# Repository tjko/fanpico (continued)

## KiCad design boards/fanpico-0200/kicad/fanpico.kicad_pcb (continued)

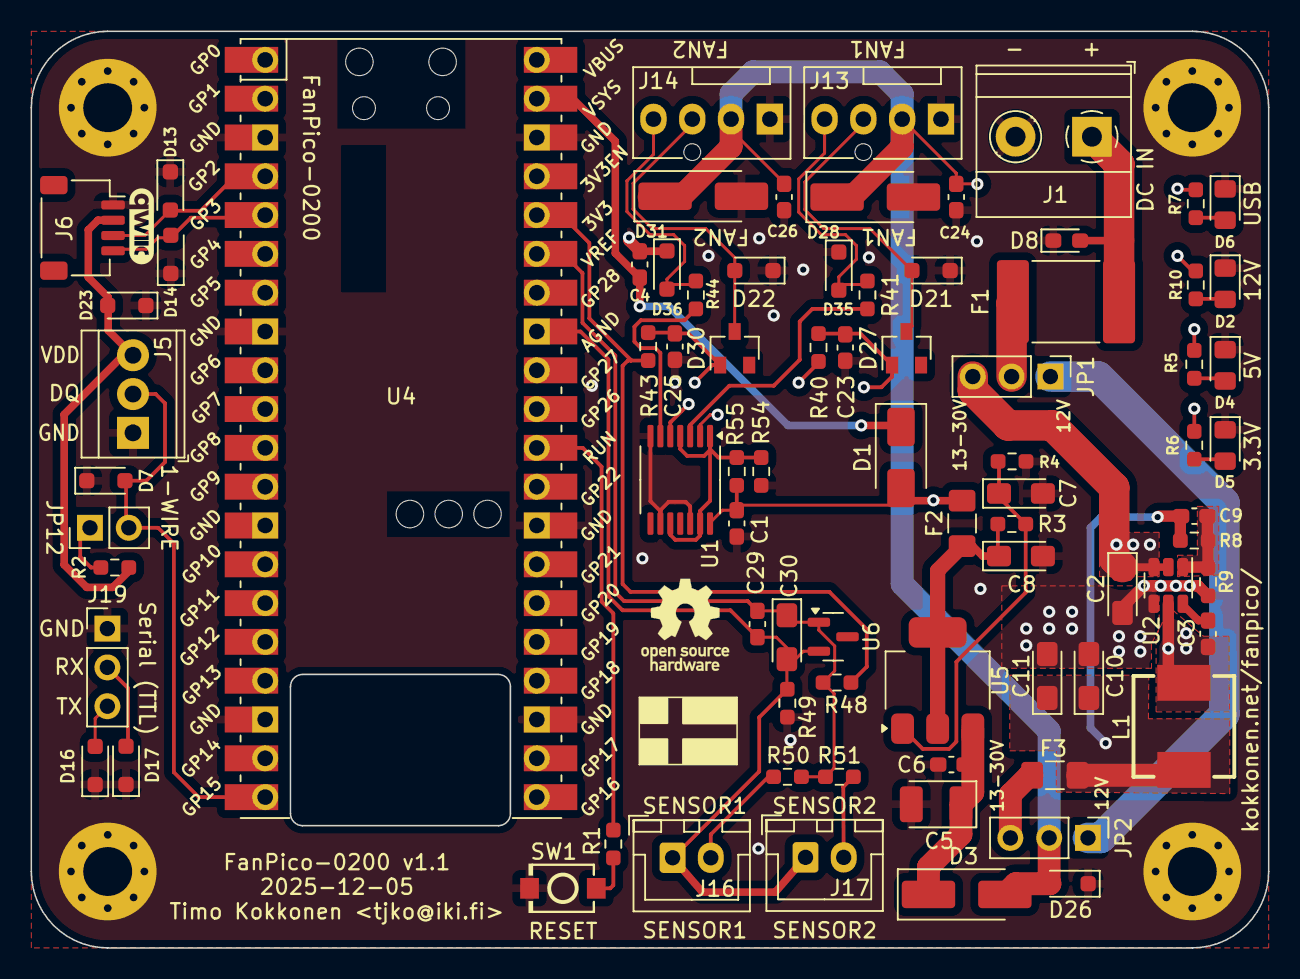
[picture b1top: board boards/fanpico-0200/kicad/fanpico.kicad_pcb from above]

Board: 4 copper layers, 81.0 x 60.0 mm, 86 parts (0 on the bottom side), 45 nets.

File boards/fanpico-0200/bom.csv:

"Reference","Value","Datasheet","Footprint","Qty","DNP","Mouser Part Number","LCSC Part Number","Manufacturer","Manufacturer Part Number","Type","Notes"
"C1,C3,C4,C6,C24,C26,C29","0.1uF 50V","~","Capacitor_SMD:C_0603_1608Metric_Pad1.08x0.95mm_HandSolder","7","","","C1591","Samsung Electro-Mechanics","CL10B104KB8NNNC","SMD",""
"C2","10uF 50V","~","Capacitor_Tantalum_SMD:CP_EIA-3216-18_Kemet-A_Pad1.58x1.35mm_HandSolder","1","","","C89632","Samsung Electro-Mechanics","CL31B106KBHNNNE","SMD",""
"C5","10uF 25V","~","Capacitor_Tantalum_SMD:CP_EIA-3528-12_Kemet-T_Pad1.50x2.35mm_HandSolder","1","","","C7194","Kyocera AVX","TAJB106K025RNJ","SMD",""
"C7,C8,C30","10uF 16V","~","Capacitor_Tantalum_SMD:CP_EIA-3216-18_Kemet-A_Pad1.58x1.35mm_HandSolder","3","","80--T491A106K016","C7171","Kyocera AVX","TAJA106K016RNJ","SMD",""
"C9","12pF 50V","~","Capacitor_SMD:C_0603_1608Metric_Pad1.08x0.95mm_HandSolder","1","","","C38523","Samsung Electro-Mechanics","CL10C120JB8NNNC","SMD",""
"C10,C11","22uF 25V","~","Capacitor_Tantalum_SMD:CP_EIA-3216-18_Kemet-A_Pad1.58x1.35mm_HandSolder","2","","","C12891","Samsung Electro-Mechanics","CL31A226KAHNNNE","SMD",""
"C23,C25","1nF 50V","~","Capacitor_SMD:C_0603_1608Metric_Pad1.08x0.95mm_HandSolder","2","","","C1588","Samsung Electro-Mechanics","CL10B102KB8NNNC","SMD",""
"D1","SM5819PL 1A 40V","~","Diode_SMD:D_SMA","1","","833-SM5819PL-TP","C669023","MCC","SM5819PL-TP","SMD",""
"D2,D4,D5,D6","LED 0805 (green)","~","LED_SMD:LED_0805_2012Metric_Pad1.15x1.40mm_HandSolder","4","","710-150080GS75000","C434432","Yongyu Photoelectric","SZYY0805G","SMD",""
"D3,D28,D31","ES1D 1A 200V","~","Diode_SMD:D_SMA_Handsoldering","3","","512-ES1D","C445494","MDD(Microdiode Semiconductor)","ES1D","SMD",""
"D7,D13,D14,D16,D17,D23","3.3V TVS","~","Diode_SMD:D_SOD-323_HandSoldering","6","","","C78439","Brightking","UDD32C03L01","SMD",""
"D8","30V TVS","~","Diode_SMD:D_0603_1608Metric_Pad1.05x0.95mm_HandSolder","1","","","C7473181","MSKSEMI","PESD0603MS30-MS","SMD",""
"D21,D22,D26","12V TVS","~","Diode_SMD:D_SOD-323_HandSoldering","3","","","C5199168","ElecSuper","UDD32C12L01-ES","SMD","C502541"
"D27,D30","BAT54(C)","~","FanPico:D_SOT-23_ANK","2","","241-BAT54C_R1_00001","C2844172","FUXINSEMI","BAT54C","SMD",""
"D35,D36","5V TVS","~","Diode_SMD:D_SOD-323_HandSoldering","2","","","C5180216","ElecSuper","PESD5V0S1BA-ES","SMD",""
"F1","Polyfuse 2A (48V)","~","Fuse:Fuse_2920_7451Metric_Pad2.10x5.45mm_HandSolder","1","","","C22399926","BHFUSE","BSMD2920-200-48V","SMD",""
"F2","Polyfuse 0.5A","~","Fuse:Fuse_1206_3216Metric_Pad1.42x1.75mm_HandSolder","1","","530-0ZCJ0050AF2E","C70072","TECHFUSE","nSMD035-16V","SMD",""
"F3","Polyfuse 1A","~","Fuse:Fuse_1206_3216Metric_Pad1.42x1.75mm_HandSolder","1","","","C7542958","LUTE","1206L100/30NR","SMD",""
"G1","qwiic_Logo","","sparkfun-qwiic:qwiic_5mm","1","","","","","","",""
"G2","Logo_Open_Hardware_Small","~","Symbol:OSHW-Logo_5.7x6mm_SilkScreen","1","","","","","","",""
"H1,H2,H3,H4","MountingHole_Pad","~","MountingHole:MountingHole_3.2mm_M3_Pad_Via","4","DNP","","","","","",""
"J1","DC Power Input","~","TerminalBlock_Phoenix:TerminalBlock_Phoenix_MKDS-1,5-2_1x02_P5.00mm_Horizontal","1","","651-1715022 ","C1509679","JILN","JL301-50002U04","THT",""
"J5","1-Wire","~","TerminalBlock_TE-Connectivity:TerminalBlock_TE_282834-3_1x03_P2.54mm_Horizontal","1","","","C68305","BOOMELE(Boom Precision Elec)","2.54-3P","THT","C5188443"
"J6","QWIIC","~","Connector_JST:JST_SH_SM04B-SRSS-TB_1x04-1MP_P1.00mm_Horizontal","1","","","C160404","JST","SM04B-SRSS-TB(LF)(SN)","SMD",""
"J13","Fan1 Output","~","Connector:FanPinHeader_1x04_P2.54mm_Vertical","1","","538-47053-1000","C240840","MOLEX","470531000","THT","KF2510-AW 3+1P"
"J14","Fan2 Output","~","Connector:FanPinHeader_1x04_P2.54mm_Vertical","1","","538-47053-1000","C240840","MOLEX","470531000","THT","KF2510-AW 3+1P"
"J16","Sensor1","~","Connector_JST:JST_XH_B2B-XH-A_1x02_P2.50mm_Vertical","1","","","C20079","BOOMELE(Boom Precision Elec)","XH-2A","THT","C33132 (Right-Angle)"
"J17","Sensor2","~","Connector_JST:JST_XH_B2B-XH-A_1x02_P2.50mm_Vertical","1","","","C20079","BOOMELE(Boom Precision Elec)","XH-2A","THT","C33132 (Right-Angle)"
"J19","Serial Console (TTL)","~","Connector_PinHeader_2.54mm:PinHeader_1x03_P2.54mm_Vertical","1","","","C2937625","XFCN","PZ254V-11-03P","THT",""
"JP12","1-Wire PullUp Enable","~","Connector_PinHeader_2.54mm:PinHeader_1x02_P2.54mm_Vertical","1","","","C492401","XFCN","PZ254V-11-02P","THT",""
"L1","10uH","~","FanPico:IND-SMD_L7.2-W6.6_GPSR07X0","1","","","C5189958","SHOU HAN","CYA0630-10UH","SMD",""
"R1,R4","1k","~","Resistor_SMD:R_0603_1608Metric_Pad0.98x0.95mm_HandSolder","2","","","C22548","YAGEO","RC0603FR-071KL","SMD",""
"R2","4.7k","~","Resistor_SMD:R_0603_1608Metric_Pad0.98x0.95mm_HandSolder","1","","","C99782","YAGEO","RC0603FR-074K7L","SMD",""
"R3,R48","330","~","Resistor_SMD:R_0603_1608Metric_Pad0.98x0.95mm_HandSolder","2","","","C105881","YAGEO","RC0603FR-07330RL","SMD",""
"R5,R7,R40,R43,R50,R51","10k","~","Resistor_SMD:R_0603_1608Metric_Pad0.98x0.95mm_HandSolder","6","","","C98220","YAGEO","RC0603FR-0710KL","SMD",""
"R6","4.99k","~","Resistor_SMD:R_0603_1608Metric_Pad0.98x0.95mm_HandSolder","1","","","C114621","YAGEO","RC0603FR-074K99L","SMD",""
"R8","422k","~","Resistor_SMD:R_0603_1608Metric_Pad0.98x0.95mm_HandSolder","1","","","C245966","YAGEO","RC0603FR-07422KL","SMD",""
"R9","30.1k","~","Resistor_SMD:R_0603_1608Metric_Pad0.98x0.95mm_HandSolder","1","","","C23000","UNI-ROYAL","0603WAF3012T5E","SMD",""
"R10","49.9k","~","Resistor_SMD:R_0603_1608Metric_Pad0.98x0.95mm_HandSolder","1","","","C114624","YAGEO","RC0603FR-0749K9L","SMD",""
"R41,R44","680","~","Resistor_SMD:R_0603_1608Metric_Pad0.98x0.95mm_HandSolder","2","","","C115415","YAGEO","RC0603JR-07680RL","SMD",""
"R49,R55","0","~","Resistor_SMD:R_0603_1608Metric_Pad0.98x0.95mm_HandSolder","2","","","C21189","UNI-ROYAL","0603WAF0000T5E","SMD",""
"R54","DNF","~","Resistor_SMD:R_0603_1608Metric_Pad0.98x0.95mm_HandSolder","1","DNP","","C21189","UNI-ROYAL","0603WAF0000T5E","SMD",""
"SW1","SW_Push","~","FanPico:SW-SMD_L3.9-W3.0-P4.45","1","","","C720477","XUNPU","TS-1088-AR02016","SMD",""
"U1","SN74AHCT126","(AHCT125 =  C36365, AHCT126 =  C155177)","Package_SO:TSSOP-14_4.4x5mm_P0.65mm","1","","","C155177","TI","SN74AHCT126PWR","SMD",""
"U2","AP63301","","FanPico:TSOT-26","1","","","C2158003","DIODES","AP63301WU-7","SMD",""
"U4","Pico W","","FanPico:RPi_Pico_PicoW_SMD_TH","1","","","","RaspberryPi","Pico W / Pico 2 W","SMD",""
"U5","SPX1117-ADJ","http://www.diodes.com/datasheets/AP1117.pdf","Package_TO_SOT_SMD:SOT-223-3_TabPin2","1","","","C67402","MaxLinear","SPX1117M3-L/TR","SMD",""
"U6","LM4040DBZ-3","http://www.ti.com/lit/ds/symlink/lm4040-n.pdf","Package_TO_SOT_SMD:SOT-23","1","","","C143326","MAXIM","LM4040AIM3-3.0+T","SMD",""

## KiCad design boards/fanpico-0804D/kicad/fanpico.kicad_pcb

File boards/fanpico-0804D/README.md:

# FANPICO-0804D PCB

PCB Size: 135mm x 81.5mm

## Change Log

v1.3
- Add QWIIC connector (to simplify connecting I2C sensors).
- Add 1-Wire connector
- Change J1 to a combination footprint (allows mounting either Floppy or DC connector).
- Slightly improved ESD protection (TVS diodes added for most connectors)

v1.2c
- Add support for using either SN74AHCT125 or SN74AHCT126 (as U1 and U2).

v1.2b
- C5 was not derated correctly. Replace with 25V part for proper derating.

v1.2
- Add alternate OLED display header with alternate pinout (J2)
- Change J18 header to 2x5 pins (with extra pins often needed for SPI displays)
- Change pull-ups to pull-downs on PWM signal pins on MBFAN inputs.

v1.1
- Add support for direct mounting either Pico or Pico W
- Remove unused footprints
- Fix errata from v1.0
- Errata:
  - JP11 Silkscreen incorrect: 10K and 100K labels should be the otherway around.

v1.0 
- First Prototye
- Based on 0804 v1.3, with added OLED (I2c) display module support
- Errata:
  - U7 pin 7 (VEE) should be grounded.
    Workaround: add solder bridge between pins 7 & 8.

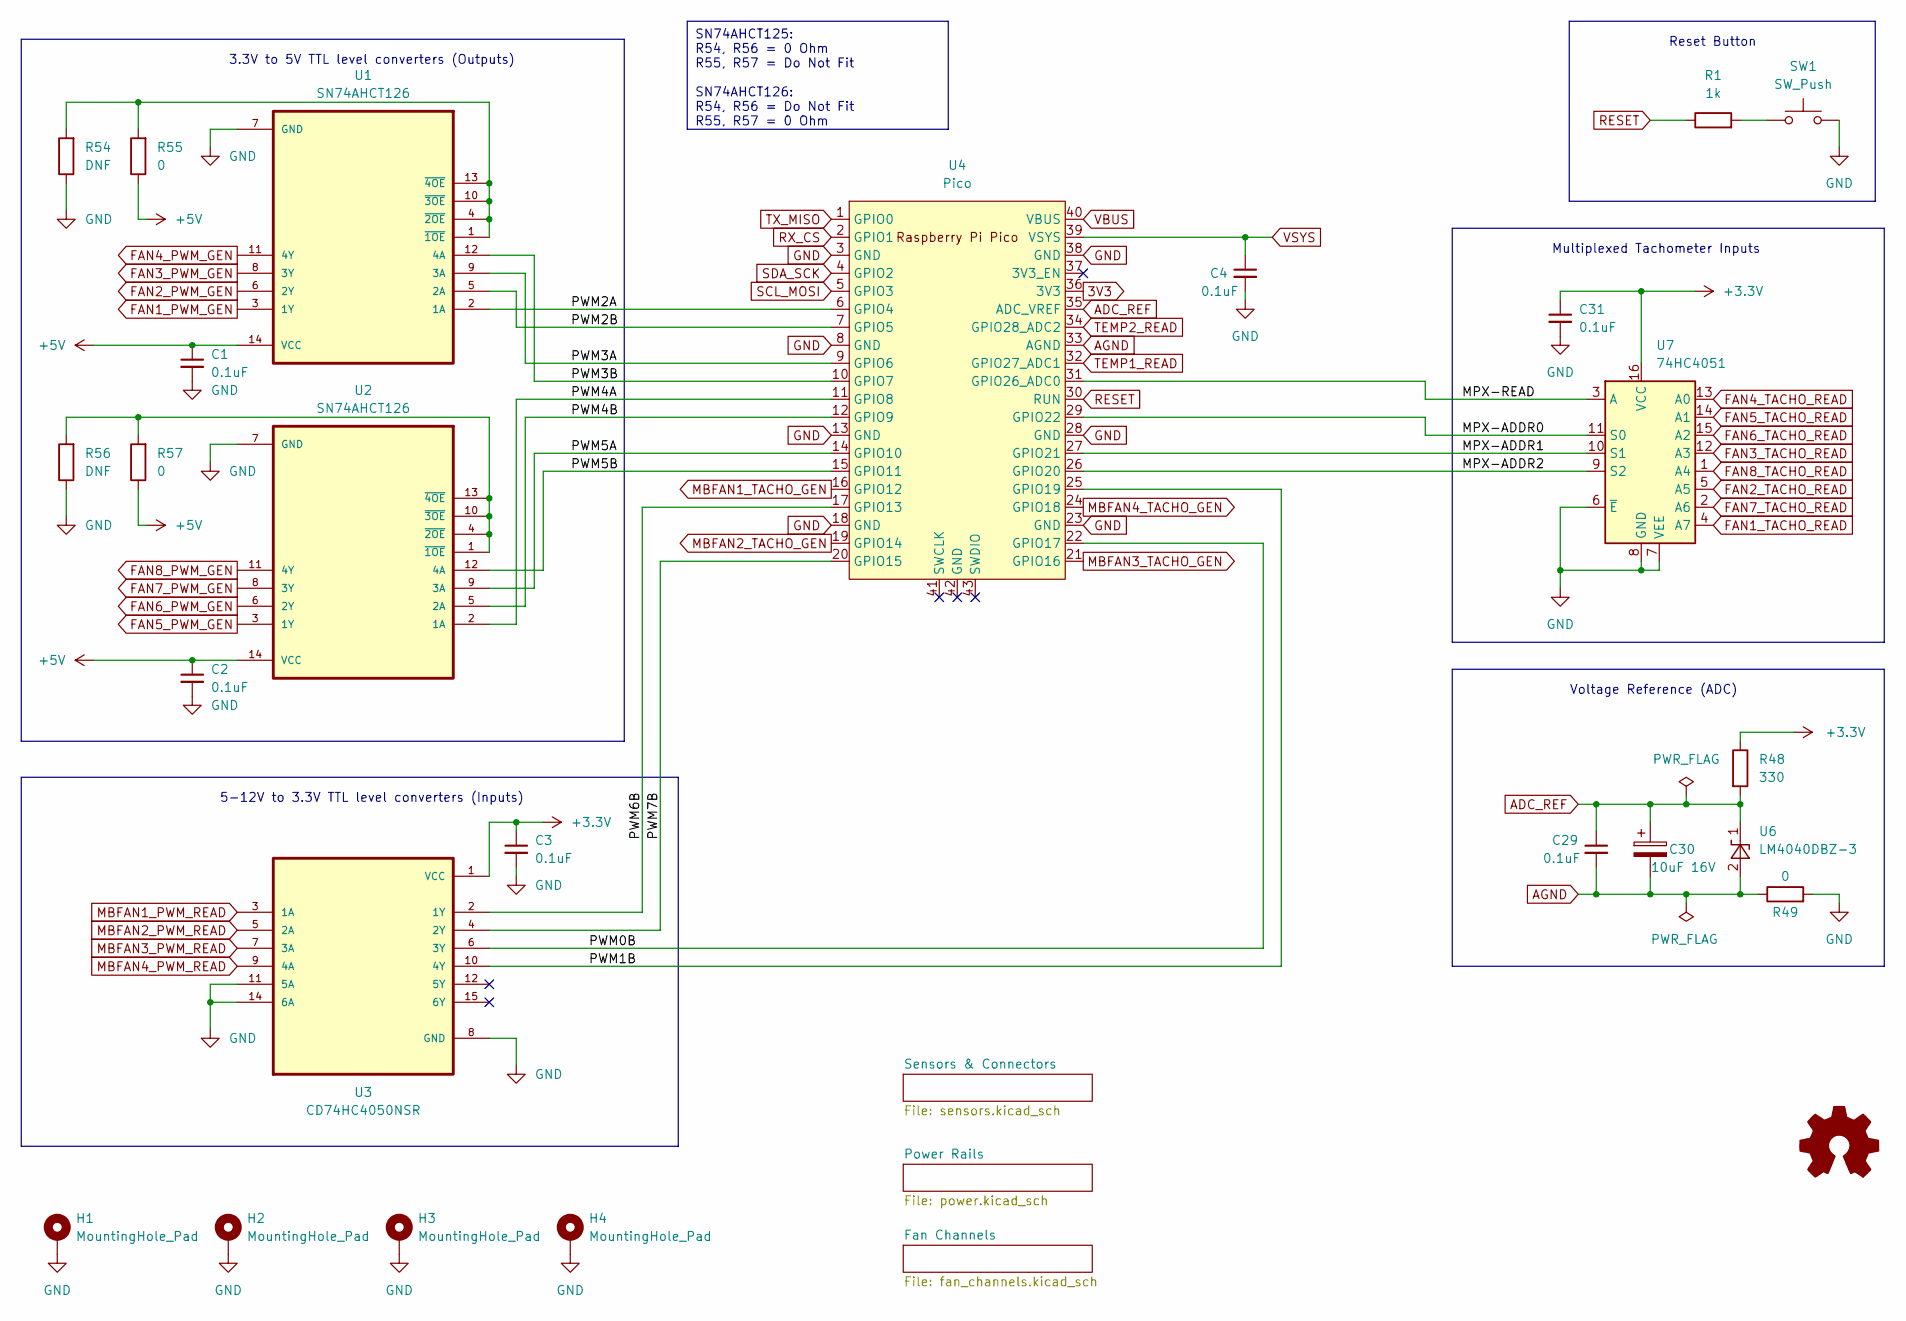
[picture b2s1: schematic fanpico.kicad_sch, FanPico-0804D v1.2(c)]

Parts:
C1, C2, C3, C4, C29, C31: 0.1uF; C_0603_1608Metric_Pad1.08x0.95mm_HandSolder; LCSC Part Number C1591
C30: 10uF 16V; CP_EIA-3216-18_Kemet-A_Pad1.58x1.35mm_HandSolder; LCSC Part Number C7171
H1, H2, H3, H4: MountingHole_Pad; MountingHole_3.2mm_M3_Pad_Via
R1: 1k; R_0603_1608Metric_Pad0.98x0.95mm_HandSolder; LCSC Part Number C22548
R48: 330; R_0603_1608Metric_Pad0.98x0.95mm_HandSolder; LCSC Part Number C105881
R49, R55, R57: 0; R_0603_1608Metric_Pad0.98x0.95mm_HandSolder; LCSC Part Number C21189
R54, R56: DNF; R_0603_1608Metric_Pad0.98x0.95mm_HandSolder
SW1: SW_Push; SW_PUSH_6mm_SMD_2
U1, U2: SN74AHCT126; SOIC-14_3.9x8.7mm_P1.27mm; LCSC Part Number C163728
U3: CD74HC4050NSR; SOIC-16_3.9x9.9mm_P1.27mm; LCSC Part Number C131932
U4: Pico; RPi_Pico_PicoW_SMD_TH
U6: LM4040DBZ-3; SOT-23; LCSC Part Number C143326
U7: 74HC4051; SOIC-16_3.9x9.9mm_P1.27mm; LCSC Part Number C9386

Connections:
3V3: C3.1, C31.1, R48.1, U3.1 (VCC), U4.36 (3V3), U7.16 (VCC); also elsewhere on the board
+5V: C1.1, C2.1, R55.1, R57.1, U1.14 (VCC), U2.14 (VCC); also elsewhere on the board
/MPX-ADDR0: U4.29 (GPIO22), U7.11 (S0)
/MPX-ADDR1: U4.27 (GPIO21), U7.10 (S1)
/MPX-ADDR2: U4.26 (GPIO20), U7.9 (S2)
/MPX-READ: U4.31 (GPIO26_ADC0), U7.3 (A)
/PWM0B: U3.6 (3Y), U4.22 (GPIO17)
/PWM1B: U3.10 (4Y), U4.25 (GPIO19)
/PWM2A: U1.2 (1A), U4.6 (GPIO4)
/PWM2B: U1.5 (2A), U4.7 (GPIO5)
/PWM3A: U1.9 (3A), U4.9 (GPIO6)
/PWM3B: U1.12 (4A), U4.10 (GPIO7)
/PWM4A: U2.2 (1A), U4.11 (GPIO8)
/PWM4B: U2.5 (2A), U4.12 (GPIO9)
/PWM5A: U2.9 (3A), U4.14 (GPIO10)
/PWM5B: U2.12 (4A), U4.15 (GPIO11)
/PWM6B: U3.2 (1Y), U4.17 (GPIO13)
/PWM7B: U3.4 (2Y), U4.20 (GPIO15)
ADC_REF: C29.1, C30.1, R48.2, U4.35 (ADC_VREF), U6.1 (K); also elsewhere on the board
AGND: C29.2, C30.2, R49.1, U4.33 (AGND), U6.2 (A); also elsewhere on the board
FAN1_PWM_GEN: U1.3 (1Y); also elsewhere on the board
FAN1_TACHO_READ: U7.4 (A7); also elsewhere on the board
FAN2_PWM_GEN: U1.6 (2Y); also elsewhere on the board
FAN2_TACHO_READ: U7.5 (A5); also elsewhere on the board
FAN3_PWM_GEN: U1.8 (3Y); also elsewhere on the board
FAN3_TACHO_READ: U7.12 (A3); also elsewhere on the board
FAN4_PWM_GEN: U1.11 (4Y); also elsewhere on the board
FAN4_TACHO_READ: U7.13 (A0); also elsewhere on the board
FAN5_PWM_GEN: U2.3 (1Y); also elsewhere on the board
FAN5_TACHO_READ: U7.14 (A1); also elsewhere on the board
FAN6_PWM_GEN: U2.6 (2Y); also elsewhere on the board
FAN6_TACHO_READ: U7.15 (A2); also elsewhere on the board
FAN7_PWM_GEN: U2.8 (3Y); also elsewhere on the board
FAN7_TACHO_READ: U7.2 (A6); also elsewhere on the board
FAN8_PWM_GEN: U2.11 (4Y); also elsewhere on the board
FAN8_TACHO_READ: U7.1 (A4); also elsewhere on the board
GND: C1.2, C2.2, C3.2, C4.2, C31.2, H1.1, H2.1, H3.1, H4.1, R49.2, R54.1, R56.1, SW1.2, U1.7 (GND), U2.7 (GND), U3.8 (GND), U3.11 (5A), U3.14 (6A), U4.3 (GND), U4.8 (GND), U4.13 (GND), U4.18 (GND), U4.23 (GND), U4.28 (GND), U4.38 (GND), U7.6 (~E), U7.7 (VEE), U7.8 (GND); also elsewhere on the board
MBFAN1_PWM_READ: U3.3 (1A); also elsewhere on the board
MBFAN1_TACHO_GEN: U4.16 (GPIO12); also elsewhere on the board
MBFAN2_PWM_READ: U3.5 (2A); also elsewhere on the board
MBFAN2_TACHO_GEN: U4.19 (GPIO14); also elsewhere on the board
MBFAN3_PWM_READ: U3.7 (3A); also elsewhere on the board
MBFAN3_TACHO_GEN: U4.21 (GPIO16); also elsewhere on the board
MBFAN4_PWM_READ: U3.9 (4A); also elsewhere on the board
MBFAN4_TACHO_GEN: U4.24 (GPIO18); also elsewhere on the board
unnamed: R1.2, SW1.1
unnamed: R54.2, R55.2, U1.1 (~1OE), U1.4 (~2OE), U1.10 (~3OE), U1.13 (~4OE)
unnamed: R56.2, R57.2, U2.1 (~1OE), U2.4 (~2OE), U2.10 (~3OE), U2.13 (~4OE)
RESET: R1.1, U4.30 (RUN)
RX_CS: U4.2 (GPIO1); also elsewhere on the board
SCL_MOSI: U4.5 (GPIO3); also elsewhere on the board
SDA_SCK: U4.4 (GPIO2); also elsewhere on the board
TEMP1_READ: U4.32 (GPIO27_ADC1); also elsewhere on the board
TEMP2_READ: U4.34 (GPIO28_ADC2); also elsewhere on the board
TX_MISO: U4.1 (GPIO0); also elsewhere on the board
VBUS: U4.40 (VBUS); also elsewhere on the board
VSYS: C4.1, U4.39 (VSYS); also elsewhere on the board

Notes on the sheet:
SN74AHCT125: R54, R56 = 0 Ohm R55, R57 = Do Not Fit SN74AHCT126: R54, R56 = Do Not Fit R55, R57 = 0 Ohm
Reset Button
3.3V to 5V TTL level converters (Outputs)
Multiplexed Tachometer Inputs
5-12V to 3.3V TTL level converters (Inputs)
Voltage Reference (ADC)

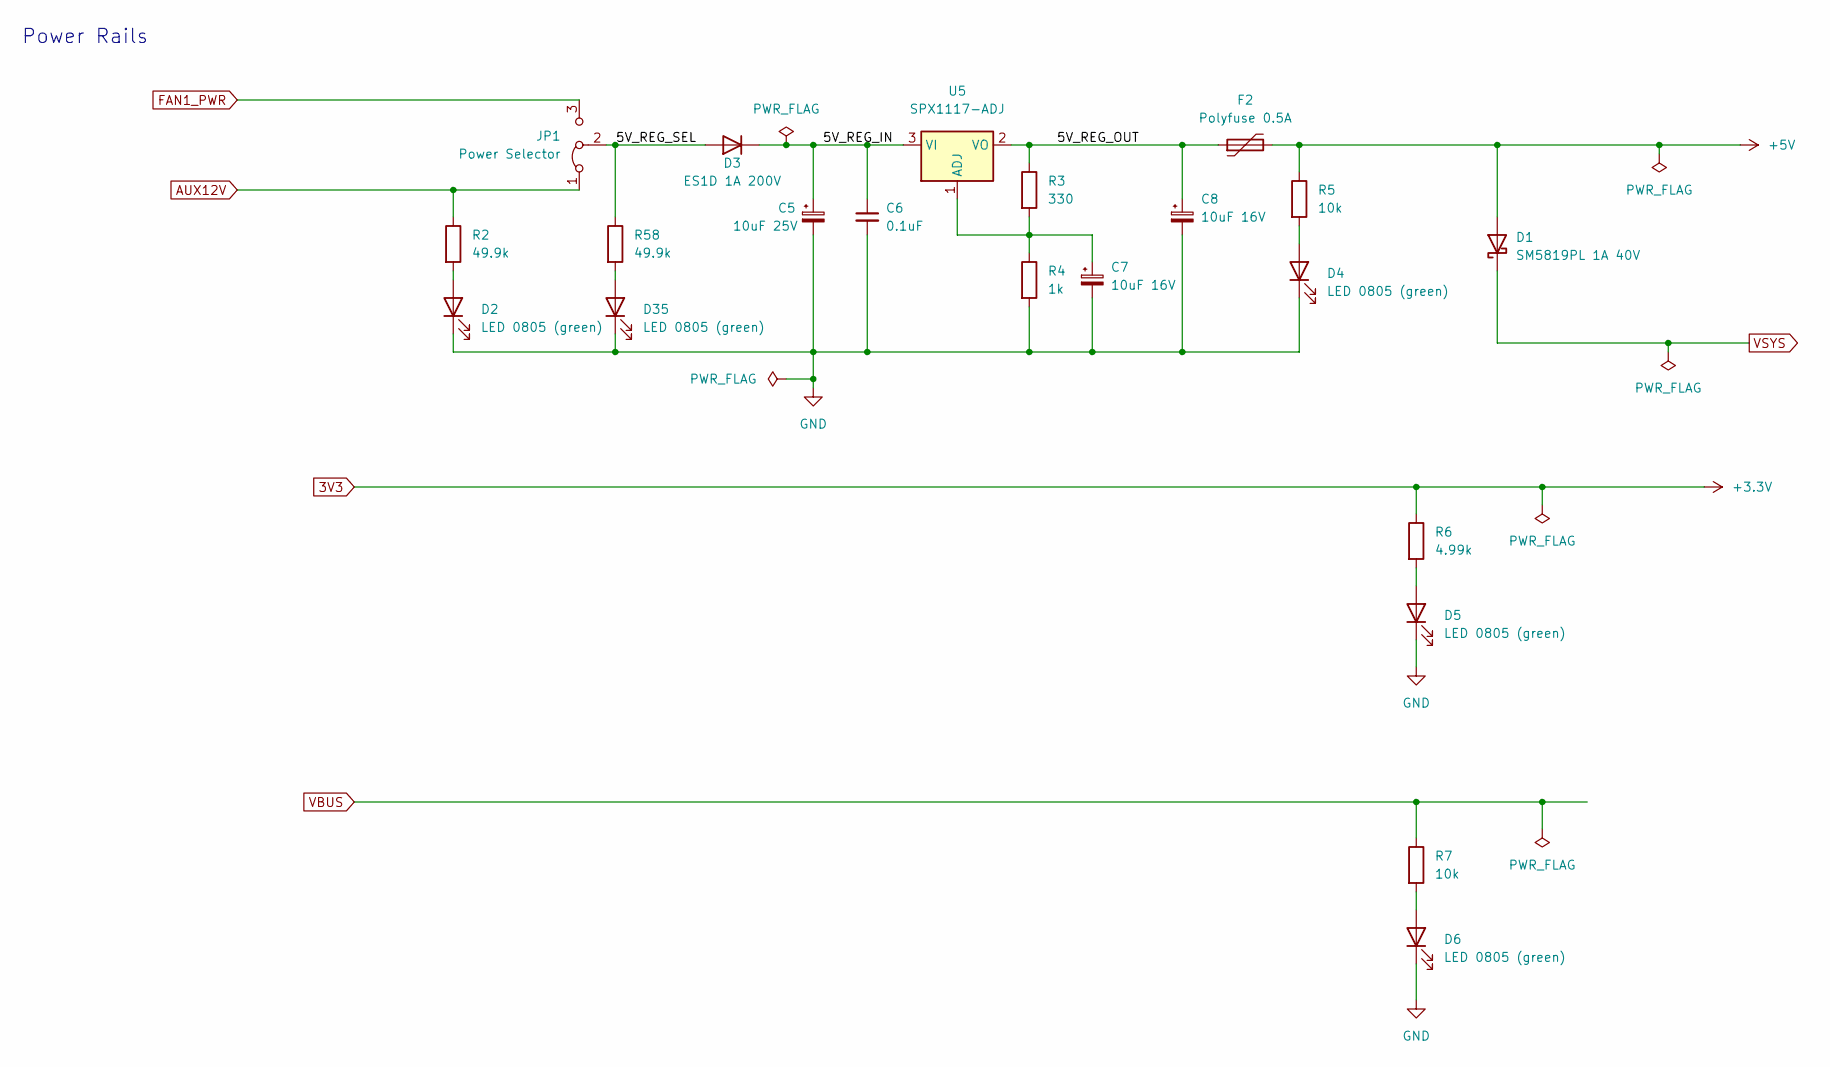
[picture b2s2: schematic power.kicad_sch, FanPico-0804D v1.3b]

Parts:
C5: 10uF 25V; CP_EIA-3528-12_Kemet-T_Pad1.50x2.35mm_HandSolder; LCSC Part Number C7194
C6: 0.1uF; C_0603_1608Metric_Pad1.08x0.95mm_HandSolder; LCSC Part Number C1591
C7, C8: 10uF 16V; CP_EIA-3216-18_Kemet-A_Pad1.58x1.35mm_HandSolder; LCSC Part Number C7171
D1: SM5819PL 1A 40V; D_SMA; LCSC Part Number C669023 or C19992592
D2, D4, D5, D6, D35: LED 0805 (green); LED_0805_2012Metric_Pad1.15x1.40mm_HandSolder; LCSC Part Number C434432
D3: ES1D 1A 200V; D_SMA_Handsoldering; LCSC Part Number C445494
F2: Polyfuse 0.5A; Fuse_1206_3216Metric_Pad1.42x1.75mm_HandSolder; LCSC Part Number C70072
JP1: Power Selector; PinHeader_1x03_P2.54mm_Vertical
R2, R58: 49.9k; R_0603_1608Metric_Pad0.98x0.95mm_HandSolder; LCSC Part Number C114624
R3: 330; R_0603_1608Metric_Pad0.98x0.95mm_HandSolder; LCSC Part Number C105881
R4: 1k; R_0603_1608Metric_Pad0.98x0.95mm_HandSolder; LCSC Part Number C22548
R5, R7: 10k; R_0603_1608Metric_Pad0.98x0.95mm_HandSolder; LCSC Part Number C98220
R6: 4.99k; R_0603_1608Metric_Pad0.98x0.95mm_HandSolder; LCSC Part Number C114621
U5: SPX1117-ADJ; SOT-223-3_TabPin2; LCSC Part Number C67402

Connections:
3V3: R6.1; also elsewhere on the board
+5V: D1.2 (A), F2.2, R5.1; also elsewhere on the board
/Power Rails/5V_REG_IN: C5.1, C6.1, D3.1 (K), U5.3 (VI)
/Power Rails/5V_REG_OUT: C8.1, F2.1, R3.1, U5.2 (VO)
/Power Rails/5V_REG_SEL: D3.2 (A), JP1.2 (C), R58.1
AUX12V: JP1.1 (A), R2.1; also elsewhere on the board
FAN1_PWR: JP1.3 (B); also elsewhere on the board
GND: C5.2, C6.2, C7.2, C8.2, D2.1 (K), D4.1 (K), D5.1 (K), D6.1 (K), D35.1 (K), R4.2; also elsewhere on the board
unnamed: D2.2 (A), R2.2
unnamed: D4.2 (A), R5.2
unnamed: D5.2 (A), R6.2
unnamed: D6.2 (A), R7.2
unnamed: D35.2 (A), R58.2
unnamed: C7.1, R3.2, R4.1, U5.1 (ADJ)
VBUS: R7.1; also elsewhere on the board
VSYS: D1.1 (K); also elsewhere on the board

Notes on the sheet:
Power Rails

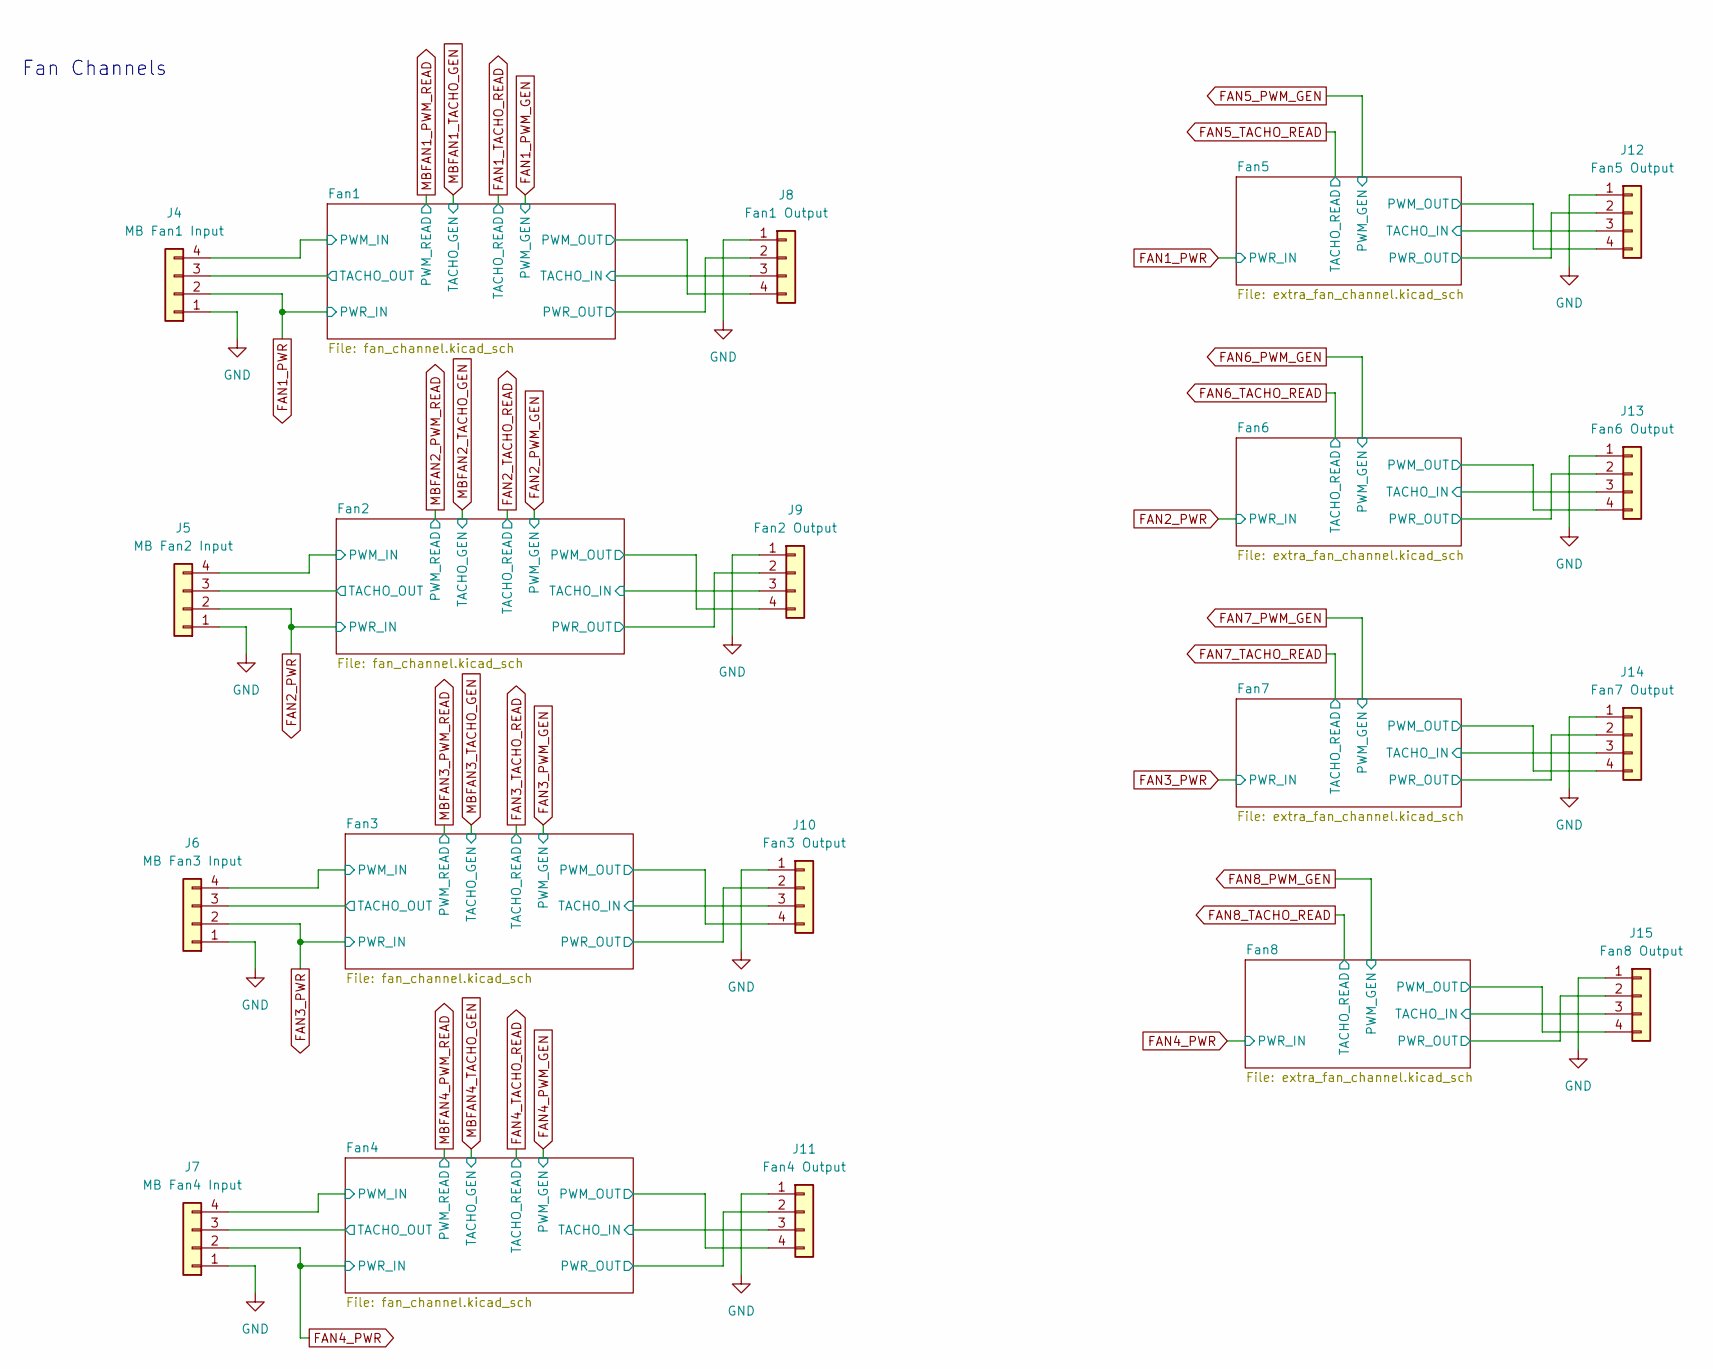
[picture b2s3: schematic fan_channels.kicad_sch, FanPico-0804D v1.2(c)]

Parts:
J4: MB Fan1 Input; FanPinHeader_1x04_P2.54mm_Vertical
J5: MB Fan2 Input; FanPinHeader_1x04_P2.54mm_Vertical
J6: MB Fan3 Input; FanPinHeader_1x04_P2.54mm_Vertical
J7: MB Fan4 Input; FanPinHeader_1x04_P2.54mm_Vertical
J8: Fan1 Output; FanPinHeader_1x04_P2.54mm_Vertical
J9: Fan2 Output; FanPinHeader_1x04_P2.54mm_Vertical
J10: Fan3 Output; FanPinHeader_1x04_P2.54mm_Vertical
J11: Fan4 Output; FanPinHeader_1x04_P2.54mm_Vertical
J12: Fan5 Output; FanPinHeader_1x04_P2.54mm_Vertical
J13: Fan6 Output; FanPinHeader_1x04_P2.54mm_Vertical
J14: Fan7 Output; FanPinHeader_1x04_P2.54mm_Vertical
J15: Fan8 Output; FanPinHeader_1x04_P2.54mm_Vertical

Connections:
/Fan Channels/Fan1/PWM_IN: J4.4; also elsewhere on the board
/Fan Channels/Fan1/PWM_OUT: J8.4; also elsewhere on the board
/Fan Channels/Fan1/PWR_OUT: J8.2; also elsewhere on the board
/Fan Channels/Fan1/TACHO_IN: J8.3; also elsewhere on the board
/Fan Channels/Fan1/TACHO_OUT: J4.3; also elsewhere on the board
/Fan Channels/Fan2/PWM_IN: J5.4; also elsewhere on the board
/Fan Channels/Fan2/PWM_OUT: J9.4; also elsewhere on the board
/Fan Channels/Fan2/PWR_OUT: J9.2; also elsewhere on the board
/Fan Channels/Fan2/TACHO_IN: J9.3; also elsewhere on the board
/Fan Channels/Fan2/TACHO_OUT: J5.3; also elsewhere on the board
/Fan Channels/Fan3/PWM_IN: J6.4; also elsewhere on the board
/Fan Channels/Fan3/PWM_OUT: J10.4; also elsewhere on the board
/Fan Channels/Fan3/PWR_OUT: J10.2; also elsewhere on the board
/Fan Channels/Fan3/TACHO_IN: J10.3; also elsewhere on the board
/Fan Channels/Fan3/TACHO_OUT: J6.3; also elsewhere on the board
/Fan Channels/Fan4/PWM_IN: J7.4; also elsewhere on the board
/Fan Channels/Fan4/PWM_OUT: J11.4; also elsewhere on the board
/Fan Channels/Fan4/PWR_OUT: J11.2; also elsewhere on the board
/Fan Channels/Fan4/TACHO_IN: J11.3; also elsewhere on the board
/Fan Channels/Fan4/TACHO_OUT: J7.3; also elsewhere on the board
/Fan Channels/Fan5/PWM_OUT: J12.4; also elsewhere on the board
/Fan Channels/Fan5/PWR_OUT: J12.2; also elsewhere on the board
/Fan Channels/Fan5/TACHO_IN: J12.3; also elsewhere on the board
/Fan Channels/Fan6/PWM_OUT: J13.4; also elsewhere on the board
/Fan Channels/Fan6/PWR_OUT: J13.2; also elsewhere on the board
/Fan Channels/Fan6/TACHO_IN: J13.3; also elsewhere on the board
/Fan Channels/Fan7/PWM_OUT: J14.4; also elsewhere on the board
/Fan Channels/Fan7/PWR_OUT: J14.2; also elsewhere on the board
/Fan Channels/Fan7/TACHO_IN: J14.3; also elsewhere on the board
/Fan Channels/Fan8/PWM_OUT: J15.4; also elsewhere on the board
/Fan Channels/Fan8/PWR_OUT: J15.2; also elsewhere on the board
/Fan Channels/Fan8/TACHO_IN: J15.3; also elsewhere on the board
FAN1_PWR: J4.2; also elsewhere on the board
FAN2_PWR: J5.2; also elsewhere on the board
FAN3_PWR: J6.2; also elsewhere on the board
FAN4_PWR: J7.2; also elsewhere on the board
GND: J4.1, J5.1, J6.1, J7.1, J8.1, J9.1, J10.1, J11.1, J12.1, J13.1, J14.1, J15.1; also elsewhere on the board

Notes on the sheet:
Fan Channels

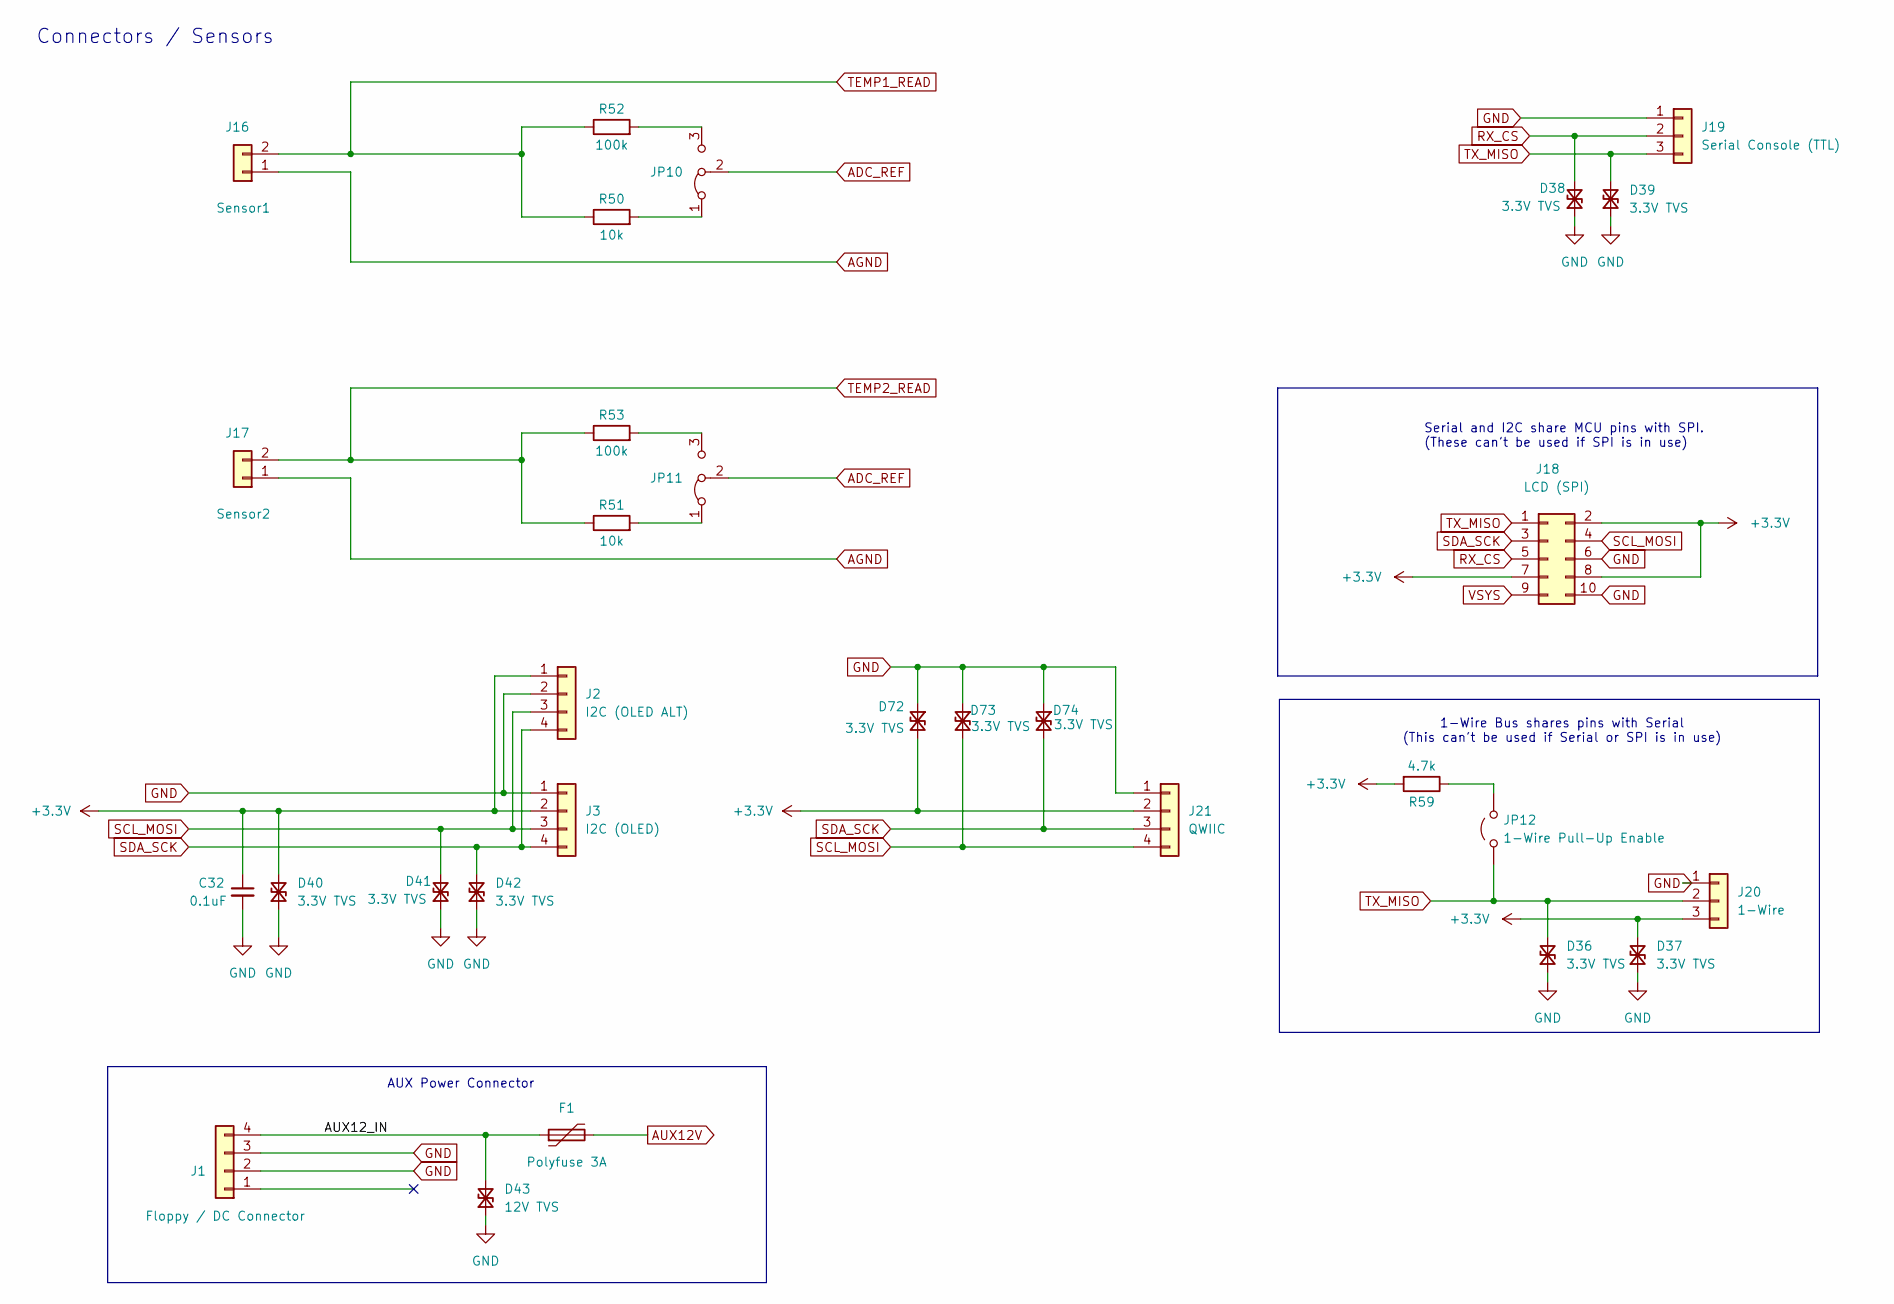
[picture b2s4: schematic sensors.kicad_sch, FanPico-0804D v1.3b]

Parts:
C32: 0.1uF; C_0603_1608Metric_Pad1.08x0.95mm_HandSolder; LCSC Part Number C1591
D36, D37, D38, D39, D40, D41, D42, D72, D73, D74: 3.3V TVS; D_SOD-323_HandSoldering; LCSC Part Number C78439
D43: 12V TVS; D_SOD-323_HandSoldering; LCSC Part Number C502541 or C5199168
F1: Polyfuse 3A; Fuse_2920_7451Metric_Pad2.10x5.45mm_HandSolder; LCSC Part Number C2977527
J1: Floppy / DC Connector; TE 171826-4 Floppy 4-pin Combo; LCSC Part Number C590635 / C720558
J2: I2C (OLED ALT); PinSocket_1x04_P2.54mm_Vertical
J3: I2C (OLED); PinSocket_1x04_P2.54mm_Vertical
J16: Sensor1; JST_XH_B2B-XH-A_1x02_P2.50mm_Vertical
J17: Sensor2; JST_XH_B2B-XH-A_1x02_P2.50mm_Vertical
J18: LCD (SPI); PinHeader_2x05_P2.54mm_Vertical
J19: Serial Console (TTL); PinHeader_1x03_P2.54mm_Vertical
J20: 1-Wire; TerminalBlock_TE_282834-3_1x03_P2.54mm_Horizontal; LCSC Part Number C68305 or C5188443
J21: QWIIC; JST_SH_SM04B-SRSS-TB_1x04-1MP_P1.00mm_Horizontal; LCSC Part Number C160404
JP10, JP11: NTC Value; PinHeader_1x03_P2.54mm_Vertical
JP12: 1-Wire Pull-Up Enable; PinHeader_1x02_P2.54mm_Vertical
R50, R51: 10k; R_0603_1608Metric_Pad0.98x0.95mm_HandSolder; LCSC Part Number C98220
R52, R53: 100k; R_0603_1608Metric_Pad0.98x0.95mm_HandSolder; LCSC Part Number C14675
R59: 4.7k; R_0603_1608Metric_Pad0.98x0.95mm_HandSolder; LCSC Part Number C99782

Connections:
3V3: C32.1, D37.2 (A2), D40.2 (A2), D72.2 (A2), J2.1, J3.2, J18.2, J18.7, J18.8, J20.3, J21.2, R59.2; also elsewhere on the board
/Sensors & Connectors/AUX12_IN: D43.2 (A2), F1.1, J1.4
ADC_REF: JP10.2 (C), JP11.2 (C); also elsewhere on the board
AGND: J16.1, J17.1; also elsewhere on the board
AUX12V: F1.2; also elsewhere on the board
GND: C32.2, D36.1 (A1), D37.1 (A1), D38.1 (A1), D39.1 (A1), D40.1 (A1), D41.1 (A1), D42.1 (A1), D43.1 (A1), D72.1 (A1), D73.1 (A1), D74.1 (A1), J1.2, J1.3, J2.2, J3.1, J18.6, J18.10, J19.1, J20.1, J21.1; also elsewhere on the board
unnamed: JP10.1 (A), R50.2
unnamed: JP10.3 (B), R52.2
unnamed: JP11.1 (A), R51.2
unnamed: JP11.3 (B), R53.2
unnamed: JP12.2 (B), R59.1
RX_CS: D38.2 (A2), J18.5, J19.2; also elsewhere on the board
SCL_MOSI: D41.2 (A2), D73.2 (A2), J2.3, J3.3, J18.4, J21.4; also elsewhere on the board
SDA_SCK: D42.2 (A2), D74.2 (A2), J2.4, J3.4, J18.3, J21.3; also elsewhere on the board
TEMP1_READ: J16.2, R50.1, R52.1; also elsewhere on the board
TEMP2_READ: J17.2, R51.1, R53.1; also elsewhere on the board
TX_MISO: D36.2 (A2), D39.2 (A2), J18.1, J19.3, J20.2, JP12.1 (A); also elsewhere on the board
VSYS: J18.9; also elsewhere on the board

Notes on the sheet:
Connectors / Sensors
AUX Power Connector
1-Wire Bus shares pins with Serial (This can't be used if Serial or SPI is in use)
Serial and I2C share MCU pins with SPI. (These can't be used if SPI is in use)
